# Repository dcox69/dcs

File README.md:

# DCS - Dryer Control System

A low-cost 3D filament dryer made from a repurposed old built-in convection oven (that is, an oven with a fan that circulates air to distribute the heat). The project includes the hardware (circuit boards), the software (the firmware), graphics, and the 3D print files for the enclosures created with OpenSCAD.

The oven I used is an old [Whirlpool AKP471/IX/01](https://www.whirlpool.fr/whirlpool-four-catalyse-encastrable-inox-akp471ix01-857747101530/p) (230V model, European only). 

Any 230V convection oven will work. The power supply is based on an HLK-5M05, which accepts an input voltage of 85 to 264 VAC, but I designed this project for 230 V, and I'm not sure if it will work properly and safely with 110 V.

&nbsp;

*front panel*

## Requirements

The logic hardware uses the small [SEEED STUDIO XIAO ESP32-C3 board](https://wiki.seeedstudio.com/XIAO_ESP32C3_Getting_Started/), a 128x64 bi-coloured (yellow/blue) SSD1306 display and an SHT31 breakout. The power supply unit uses an Hi-Link HLK-5M05, OMRON G2RL-1A-E-DC5 relays, AO3400A Mosfets, a few passive components, JST & other connectors. 

All the components were purchased from AliExpress and Mouser. The total cost is low: the oven was salvaged (one of the two heating elements was burned out), and the parts cost about 40€ (~44 US$) (including the 3D filament, copper plates & ferric chloride). 

&nbsp;

*Close-up of the enclosure containing the SHT31 inside the oven (printed in ASA)*

## Features

- Oven PID controlled firmware, with temperature prediction and duty cycle control (The PID must be fine-tuned based on the equipment, because the ovens heating elements have enormous thermal inertia)

- Designed for high thermal inertia devices

- Basic user interface using a rotary EC11 + touch switch & an SSD1306

## Firmware

- Project based on ESP-IDF 5.5.x & FreeRTOS.

- I'm using VS Code with the ESP-IDF extension

- The projet uses some older releases of my [embedded libraries](https://github.com/dcox69/libs "dcox69 libs"), in the [components](firmware/components/) directory.

## Hardware

see [README.md](hardware/ "Hardware")

&nbsp;

 *Back panel board*

&nbsp;

 *PSU board*

## Usage

&nbsp;

*front panel screen close-up*
&nbsp;

Rotate the EC11 to select an item, click to open that item, then rotate to choose from the options, and finally click to confirm. 

There are only two settings: temperature setting (5°C increments) and drying time (30-minute increments). The last settings used are saved in flash memory. 

When using the oven, leave the door slightly ajar so that humidity can escape and does not remain trapped inside the oven.

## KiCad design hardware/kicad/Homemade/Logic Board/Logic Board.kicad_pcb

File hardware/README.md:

# DCS - Dryer Control System Hardware

A low-cost 3D filament dryer made from a repurposed old built-in convection oven. 

Contains the schematics for the two homemade PCBs (power supply and logic) into the Homemade/ folder. 

The double-sided PCBs are designed entirely for DIY fabrication using the iron method with thermal transfer paper and etched with ferric chloride. Large vias are used to connect one side to the other and link the ground planes.

The logic hardware uses the small [SEEED STUDIO XIAO ESP32-C3 board](https://wiki.seeedstudio.com/XIAO_ESP32C3_Getting_Started/), a 128x64 bi-coloured (yellow/blue) SSD1306 display and an SHT31 breakout. The power supply unit uses an Hi-Link HLK-5M05, OMRON G2RL-1A-E-DC5 relays, AO3400A Mosfets, a few passive components, JST & other connectors. For heater relay feedback, i've used an optocoupler module like this one :

All the components were purchased from AliExpress and Mouser. The total cost is low: the oven was salvaged (one of the two heating elements was burned out), and the parts cost about 40€ (~44 US$) (including the 3D filament, copper plates & ferric chloride). 

The oven I used is an old [Whirlpool AKP471/IX/01](https://www.whirlpool.fr/whirlpool-four-catalyse-encastrable-inox-akp471ix01-857747101530/p) (230V model, European only), and I only used the top heating element, which is rated at 1400W. At 230V, that’s about 6A, which is easily manageable. Of course, any 230V convection oven will work. The power supply is based on an HLK-5M05, which accepts an input voltage of 85 to 264 VAC, but I designed this project for 230 V, and I'm not sure if it will work properly and safely with 110 V. 

### *important notice*

> On the ESP32-C3, GPIOs 2, 8 et 9 are strapping pins. I'm using GPIO 8, which is LOW at boot on the XIAO ESP32C3 board. GPIO 9 is starting HIGH at boot (can be pulled LOW by the BOOT switch).
>
> The GPIOs 20 & 21 are used by UART, and they are pulled HIGH at boot, so the FAN & LIGHT relays are pulled ON at boot for a very short time. To avoid this, I should have used GPIO 8, 9, 20 or 21 for I²C (SDA/SCL), and GPIO 3, 4, 5, 6, 7, 10 for RELAYS & EC11, which is not enough. (EC11 needs 3 pins, and relays needs 4).
>
> So the XIAO ESP32C3 board was not the best choice for this project, a V2 logical board should be based on another board with more available free / non strapping GPIOs.

&nbsp;

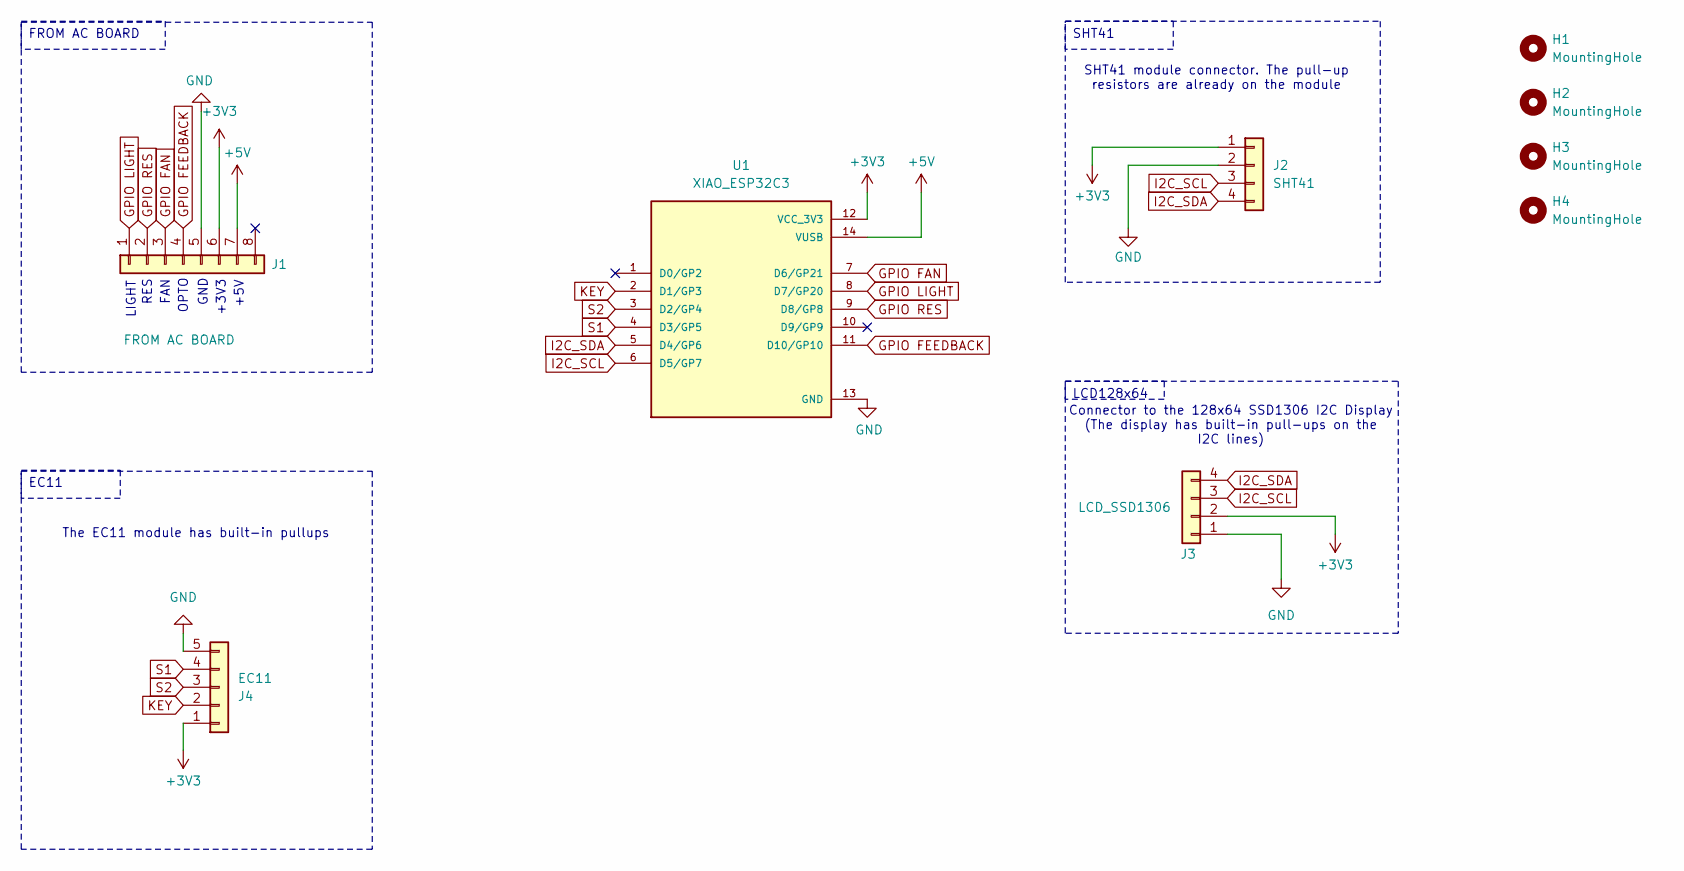
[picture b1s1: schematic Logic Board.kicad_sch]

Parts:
H1, H2, H3, H4: MountingHole; MountingHole__MountingHole_2.7mm_M2.5_4eeb3e5dd5
J1: FROM AC BOARD; JST_XH_S8B-AE-23mmx7.5mm-XH-A_1x08_P2.50mm_Horizontal
J2: SHT41; JST_XH_B4B-XH-A_1x04_P2.50mm_Vertical
J3: LCD_SSD1306; JST_XH_B4B-XH-A_1x04_P2.50mm_Vertical
J4: EC11; JST_XH_S5B-XH-A_1x05_P2.50mm_Horizontal
U1: XIAO_ESP32C3; MODULE_XIAO_ESP32C3; PARTREV 23/05/2022

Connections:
+3V3: J1.6, J2.1, J3.2, J4.1, U1.12 (VCC_3V3)
+5V: J1.7, U1.14 (VUSB)
GND: J1.5, J2.2, J3.1, J4.5, U1.13 (GND)
GPIO FAN: J1.3, U1.7 (D6/GP21)
GPIO FEEDBACK: J1.4, U1.11 (D10/GP10)
GPIO LIGHT: J1.1, U1.8 (D7/GP20)
GPIO RES: J1.2, U1.9 (D8/GP8)
I2C_SCL: J2.3, J3.3, U1.6 (D5/GP7)
I2C_SDA: J2.4, J3.4, U1.5 (D4/GP6)
KEY: J4.2, U1.2 (D1/GP3)
S1: J4.4, U1.4 (D3/GP5)
S2: J4.3, U1.3 (D2/GP4)

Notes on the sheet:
+3V3
GND
FAN
LIGHT
RES
SHT41 module connector. The pull-up resistors are already on the module
The EC11 module has built-in pullups
Connector to the 128x64 SSD1306 I2C Display (The display has built-in pull-ups on the I2C lines)
OPTO
+5V
FROM AC BOARD
SHT41
EC11
LCD128x64

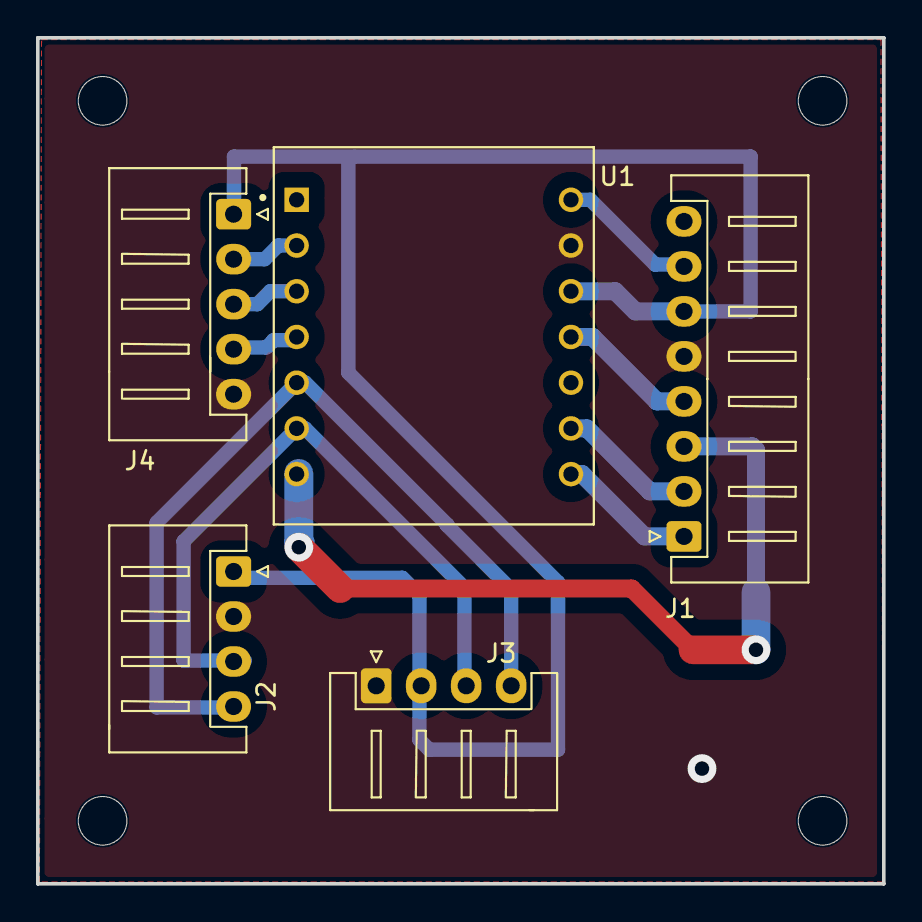
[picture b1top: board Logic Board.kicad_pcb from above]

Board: 2 copper layers, 47.0 x 47.0 mm, 9 parts (0 on the bottom side), 12 nets.

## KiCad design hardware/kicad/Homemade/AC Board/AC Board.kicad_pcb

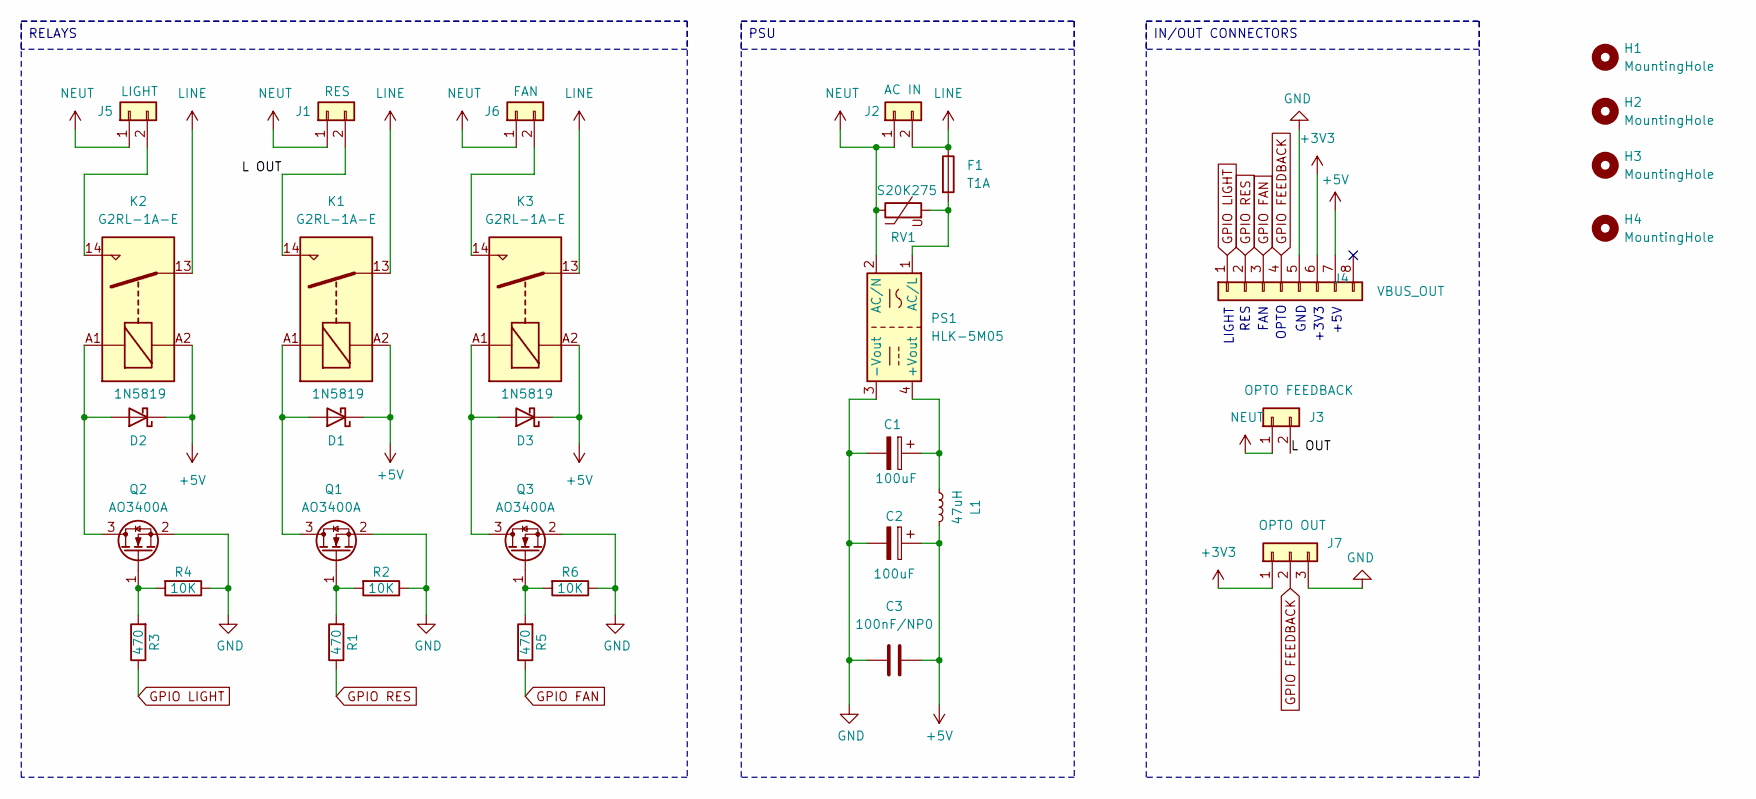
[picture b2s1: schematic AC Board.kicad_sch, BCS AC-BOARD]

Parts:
C1, C2: 100uF; Capacitor_THT__CP_Radial_D6.3mm_P2.50mm_30c41b2cbd
C3: 100nF/NP0; Capacitor_THT__C_Rect_L7.0mm_W2.0mm_P5.00mm_07977cdd8c
D1, D2, D3: 1N5819; Diode_THT__D_DO-41_SOD81_P10.16mm_Horizontal_8c01c841ae
F1: T1A; Fuse__Fuseholder_TR5_Littelfuse_No560_No460_ae15df276f
H1, H2, H3, H4: MountingHole; MountingHole__MountingHole_2.7mm_M2.5_4eeb3e5dd5
J1: RES; TerminalBlock_VIS_Ali_20x14.5_P10.0mm
J2: AC IN; TerminalBlock_VIS_Ali_20x14.5_P10.0mm
J3: OPTO FEEDBACK; TerminalBlock_Phoenix__TerminalBlock_Phoenix_MKDS-1,5-2-5.0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
J4: VBUS_OUT; JST_XH_S8B-AE-23mmx7.5mm-XH-A_1x08_P2.50mm_Horizontal
J5: LIGHT; TerminalBlock_Phoenix__TerminalBlock_Phoenix_MKDS-1,5-2-5.0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
J6: FAN; TerminalBlock_Phoenix__TerminalBlock_Phoenix_MKDS-1,5-2-5.0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
J7: OPTO OUT; JST_XH_S3B-AE-10mmx7.5mm-XH-A_1x03_P2.50mm_Horizontal
K1, K2, K3: G2RL-1A-E; Relay_THT__Relay_SPST_Omron_G2RL-1A-E_d4b3297544
L1: 47uH; Inductor_CD54_AE_SMD
PS1: HLK-5M05; Converter_ACDC__Converter_ACDC_Hi-Link_HLK-5Mxx_13fa4f5f48
Q1, Q2, Q3: AO3400A; Package_TO_SOT_SMD__SOT-23_e3fc7a82cd
R1, R3, R5: 470; Resistor_SMD__R_0805_2012Metric_Pad1.20x1.40mm_HandSolder_5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
R2, R4, R6: 10K; Resistor_SMD__R_0805_2012Metric_Pad1.20x1.40mm_HandSolder_5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
RV1: S20K275; Varistor__RV_Disc_D21.5mm_W4.3mm_P10mm_7e9e8648c4

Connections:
+3V3: J4.6, J7.1
+5V: C2.1, C3.2, D1.1 (K), D2.1 (K), D3.1 (K), J4.7, K1.A2, K2.A2, K3.A2, L1.2
/L OUT: J1.2, J3.2, K1.14
GND: C1.2, C2.2, C3.1, J4.5, J7.3, PS1.3 (-Vout), Q1.2 (S), Q2.2 (S), Q3.2 (S), R2.1, R4.1, R6.1
GPIO FAN: J4.3, R5.1
GPIO FEEDBACK: J4.4, J7.2
GPIO LIGHT: J4.1, R3.1
GPIO RES: J4.2, R1.1
LINE: F1.1, J2.2, K1.13, K2.13, K3.13
NEUT: J1.1, J2.1, J3.1, J5.1, J6.1, PS1.2 (AC/N), RV1.1
unnamed: D1.2 (A), K1.A1, Q1.3 (D)
unnamed: D2.2 (A), K2.A1, Q2.3 (D)
unnamed: D3.2 (A), K3.A1, Q3.3 (D)
unnamed: J5.2, K2.14
unnamed: J6.2, K3.14
unnamed: C1.1, L1.1, PS1.4 (+Vout)
unnamed: F1.2, PS1.1 (AC/L), RV1.2
unnamed: Q1.1 (G), R1.2, R2.2
unnamed: Q2.1 (G), R3.2, R4.2
unnamed: Q3.1 (G), R5.2, R6.2

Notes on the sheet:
+5V
OPTO
LIGHT
+3V3
GND
FAN
RES
IN/OUT CONNECTORS
RELAYS
PSU

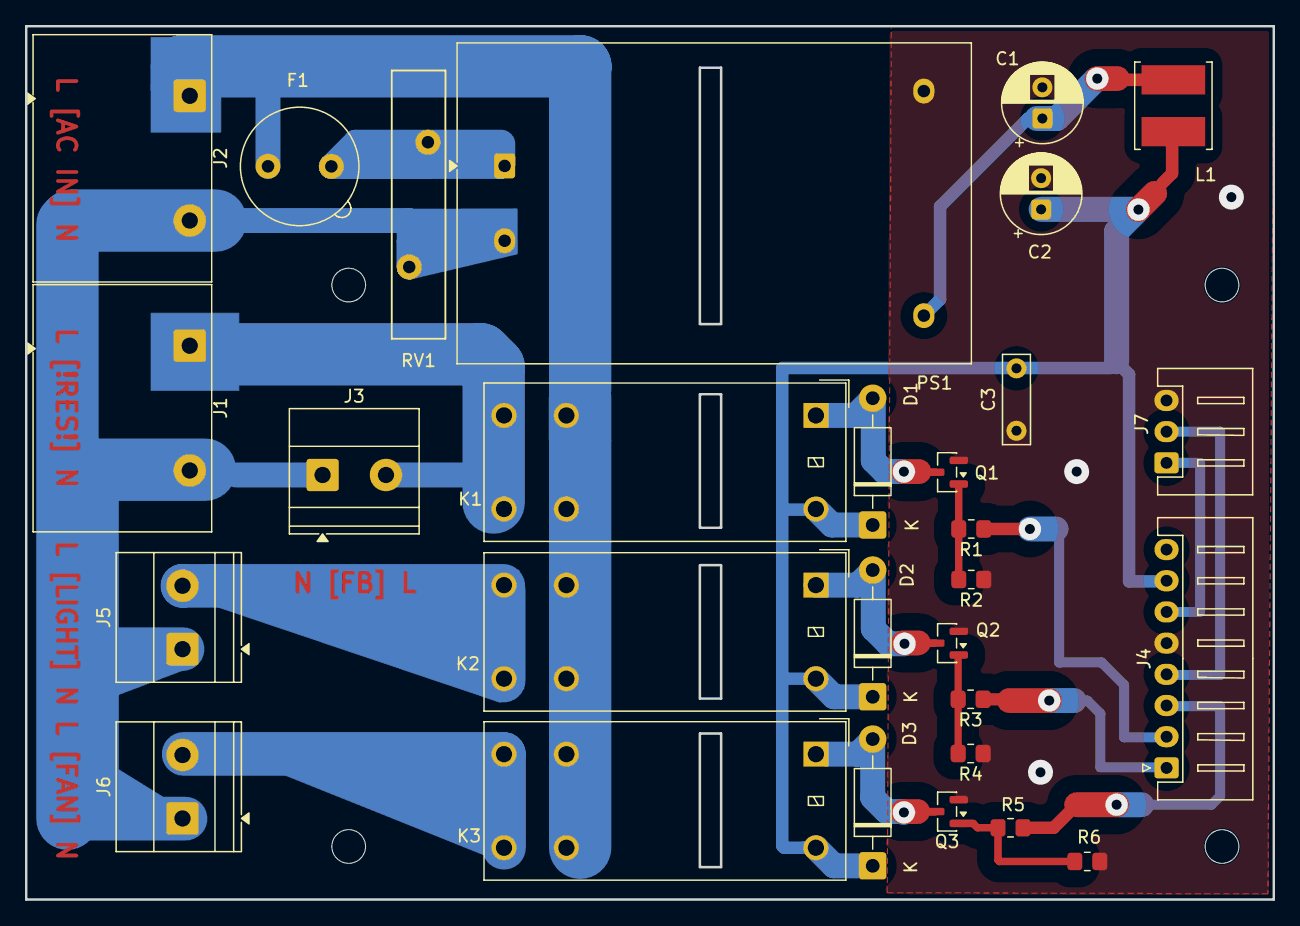
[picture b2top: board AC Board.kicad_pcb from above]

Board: 2 copper layers, 100.0 x 70.0 mm, 33 parts (0 on the bottom side), 20 nets.
